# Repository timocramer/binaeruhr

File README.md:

This is a binary pocket watch, made with an atmega48pa. The enclosure is from a cheap pocket watch, mass produced in China and sold via Ebay or Aliexpress.

# build your own

Have a look at the [construction manual](construction-manual.md) if you want to build your own.

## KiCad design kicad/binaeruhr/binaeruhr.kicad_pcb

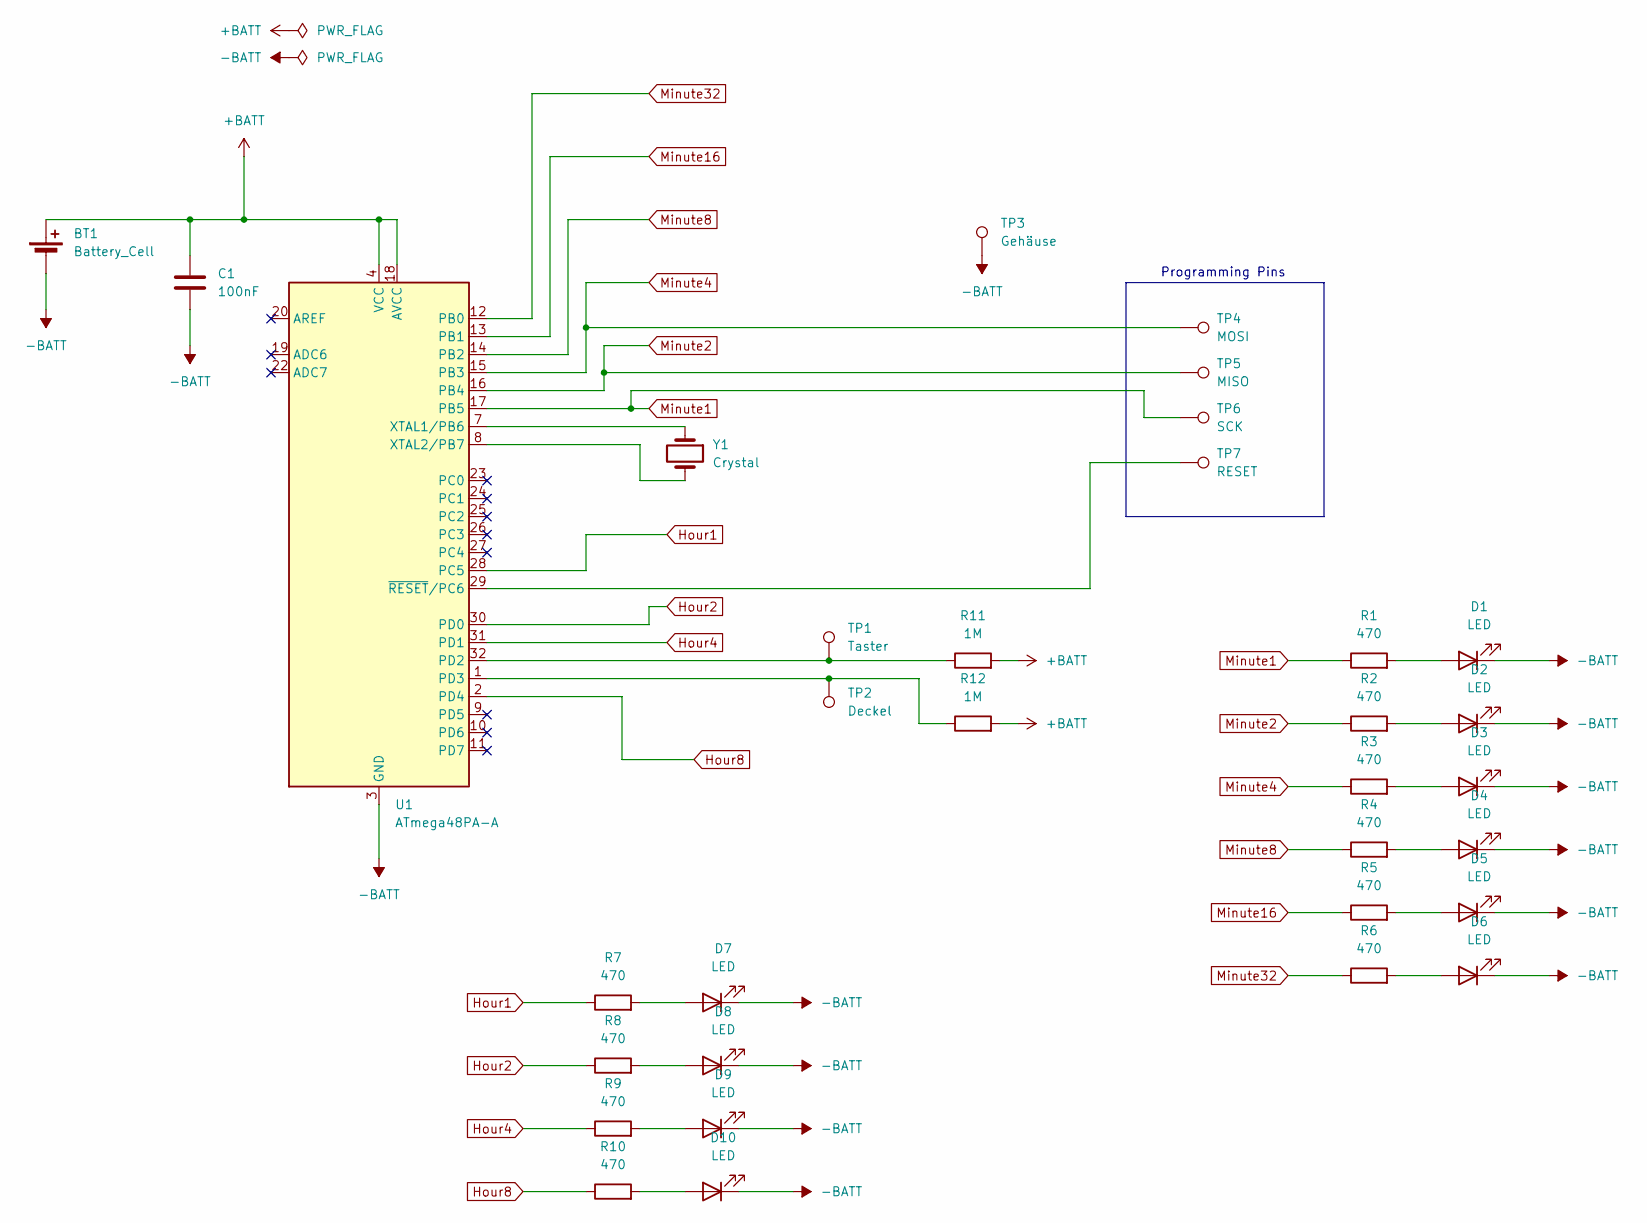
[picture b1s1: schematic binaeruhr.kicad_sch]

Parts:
BT1: Battery_Cell; BatteryHolder_Keystone_3002_1x2032
C1: 100nF; C_0805_2012Metric_Pad1.18x1.45mm_HandSolder
D1, D2, D3, D4, D5, D6, D7, D8, D9, D10: LED; LED_0805_2012Metric_Pad1.15x1.40mm_HandSolder
R1, R2, R3, R4, R5, R6, R7, R8, R9, R10: 470; R_0805_2012Metric_Pad1.20x1.40mm_HandSolder
R11, R12: 1M; R_0805_2012Metric_Pad1.20x1.40mm_HandSolder
TP1: Taster; TestPoint_Pad_4.0x4.0mm
TP2: Deckel; TestPoint_Pad_4.0x4.0mm
TP3: Gehäuse; TestPoint_Pad_2.0x2.0mm
TP4: MOSI; TestPoint_Pad_1.0x1.0mm
TP5: MISO; TestPoint_Pad_1.0x1.0mm
TP6: SCK; TestPoint_Pad_1.0x1.0mm
TP7: RESET; TestPoint_Pad_1.0x1.0mm
U1: ATmega48PA-A; TQFP-32_7x7mm_P0.8mm
Y1: Crystal; Crystal_SMD_MicroCrystal_MS1V-T1K

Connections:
+BATT: BT1.1 (+), C1.1, R11.2, R12.2, U1.4 (VCC), U1.6 (VCC), U1.18 (AVCC)
-BATT: BT1.2 (-), C1.2, D1.1 (K), D2.1 (K), D3.1 (K), D4.1 (K), D5.1 (K), D6.1 (K), D7.1 (K), D8.1 (K), D9.1 (K), D10.1 (K), TP3.1, U1.3 (GND), U1.5 (GND), U1.21 (GND)
Hour1: R7.1, U1.28 (PC5)
Hour2: R8.1, U1.30 (PD0)
Hour4: R9.1, U1.31 (PD1)
Hour8: R10.1, U1.2 (PD4)
Minute1: R1.1, TP6.1, U1.17 (PB5)
Minute2: R2.1, TP5.1, U1.16 (PB4)
Minute4: R3.1, TP4.1, U1.15 (PB3)
Minute8: R4.1, U1.14 (PB2)
Minute16: R5.1, U1.13 (PB1)
Minute32: R6.1, U1.12 (PB0)
unnamed: D1.2 (A), R1.2
unnamed: D2.2 (A), R2.2
unnamed: D3.2 (A), R3.2
unnamed: D4.2 (A), R4.2
unnamed: D5.2 (A), R5.2
unnamed: D6.2 (A), R6.2
unnamed: D7.2 (A), R7.2
unnamed: D8.2 (A), R8.2
unnamed: D9.2 (A), R9.2
unnamed: D10.2 (A), R10.2
unnamed: R11.1, TP1.1, U1.32 (PD2)
unnamed: R12.1, TP2.1, U1.1 (PD3)
unnamed: U1.7 (XTAL1/PB6), Y1.1
unnamed: U1.8 (XTAL2/PB7), Y1.2
unnamed: TP7.1, U1.29 (~RESET/PC6)

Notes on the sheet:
Programming Pins

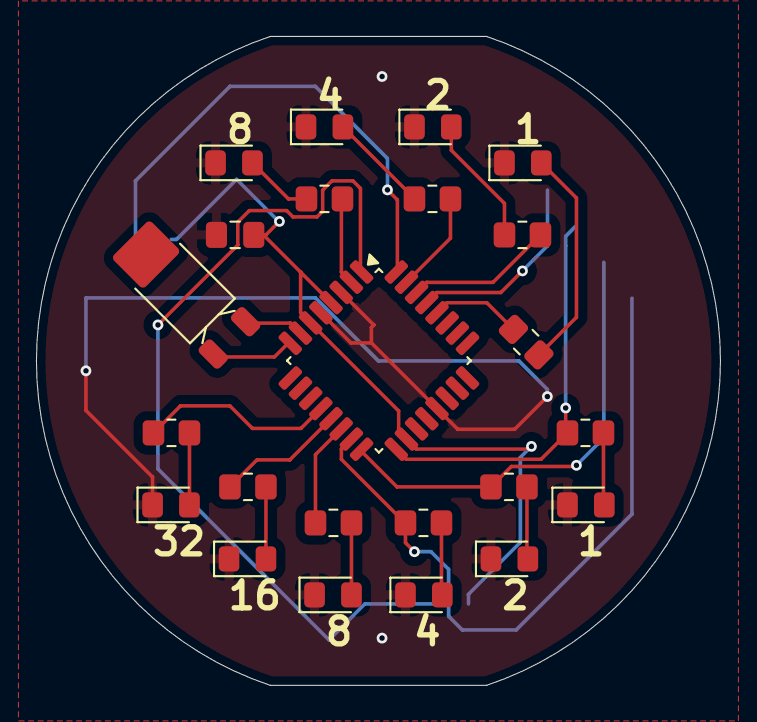
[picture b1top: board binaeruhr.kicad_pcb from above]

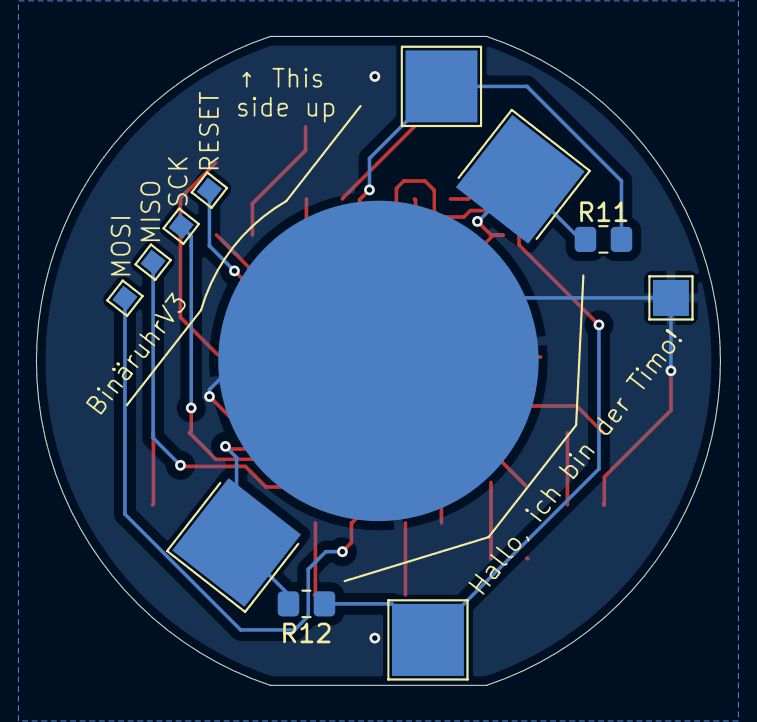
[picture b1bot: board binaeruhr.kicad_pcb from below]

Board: 2 copper layers, 38.0 x 36.0 mm, 33 parts (10 on the bottom side), 27 nets.

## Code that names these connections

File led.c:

#include "led.h"

#include <avr/io.h>

void led_init_outputs() {
    DDRD |= _BV(PD4); // hour8
    DDRD |= _BV(PD2); // hour4
    DDRD |= _BV(PD1); // hour2
    DDRC |= _BV(PC5); // hour1
    
    DDRB |= _BV(PB0); // minute32
    DDRB |= _BV(PB1); // minute16
    DDRB |= _BV(PB2); // minute8
    DDRB |= _BV(PB3); // minute4
    DDRB |= _BV(PB4); // minute2
    DDRB |= _BV(PB5); // minute1
}

static void hour8_on() {
    PORTD |= _BV(PD4);
}

static void hour8_off() {
    PORTD &= ~_BV(PD4);
}

static void hour4_on() {
    PORTD |= _BV(PD2);
}

static void hour4_off() {
    PORTD &= ~_BV(PD2);
}

static void hour2_on() {
    PORTD |= _BV(PD1);
}

static void hour2_off() {
    PORTD &= ~_BV(PD1);
}

static void hour1_on() {
    PORTC |= _BV(PC5);
}

static void hour1_off() {
    PORTC &= ~_BV(PC5);
}

void led_show_hours(uint8_t hours) {
    if(hours & 8) {
        hour8_on();
    } else {
        hour8_off();
    }
    if(hours & 4) {
        hour4_on();
    } else {
        hour4_off();
    }
    if(hours & 2) {
        hour2_on();
    } else {
        hour2_off();
    }
    if(hours & 1) {
        hour1_on();
    } else {
        hour1_off();
    }
}

static void minute32_on() {
    PORTB |= _BV(PB0);
}

static void minute32_off() {
    PORTB &= ~_BV(PB0);
}

static void minute16_on() {
    PORTB |= _BV(PB1);
}

static void minute16_off() {
    PORTB &= ~_BV(PB1);
}

static void minute8_on() {
    PORTB |= _BV(PB2);
}

static void minute8_off() {
    PORTB &= ~_BV(PB2);
}

static void minute4_on() {
    PORTB |= _BV(PB3);
}

static void minute4_off() {
    PORTB &= ~_BV(PB3);
}

static void minute2_on() {
    PORTB |= _BV(PB4);
}

static void minute2_off() {
    PORTB &= ~_BV(PB4);
}

static void minute1_on() {
    PORTB |= _BV(PB5);
}

static void minute1_off() {
    PORTB &= ~_BV(PB5);
}

void led_show_minutes(uint8_t minutes) {
    if(minutes & 32) {
        minute32_on();
    } else {
        minute32_off();
    }
    if(minutes & 16) {
        minute16_on();
    } else {
        minute16_off();
    }
    if(minutes & 8) {
        minute8_on();
    } else {
        minute8_off();
    }
    if(minutes & 4) {
        minute4_on();
    } else {
        minute4_off();
    }
    if(minutes & 2) {
        minute2_on();
    } else {
        minute2_off();
    }
    if(minutes & 1) {
        minute1_on();
    } else {
        minute1_off();
    }
}

void led_show_time(uint8_t hours, uint8_t minutes) {
    led_show_hours(hours);
    led_show_minutes(minutes);
}

void led_hours_off() {
    hour8_off();
    hour4_off();
    hour2_off();
    hour1_off();
}

void led_minutes_off() {
    minute32_off();
    minute16_off();
    minute8_off();
    minute4_off();
    minute2_off();
    minute1_off();
}

void leds_off() {
	led_hours_off();
	led_minutes_off();
}

void leds_on() {
    hour8_on();
    hour4_on();
    hour2_on();
    hour1_on();
    minute32_on();
    minute16_on();
    minute8_on();
    minute4_on();
    minute2_on();
    minute1_on();
}

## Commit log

2024-06-30 use correct function name, we disable the ac not adc
2024-07-01 changes in timer functions
    - fix prescaler 8 bits and add "prescaler" 1
    - more efficient implementation of current_timer_prescaler
    - reset timer conditionally but set timer bits unconditionally
2024-07-01 remove unused function
2024-07-01 alternative blink pattern on startup
2024-07-01 whitespace
2024-07-01 add function to init unused pins
2024-07-02 move going to time setting mode into an own function
2024-07-02 consistent indentation of switch cases
2024-07-02 use break instead of return so code after the switch is executed (no idea why the compiler was not warning this time)
2024-07-03 make constants uppercase, move some constants out of function
2024-07-03 use led pins for hour2 and hour4 that are used on the pcb
2024-07-04 reset timer on startup
2024-07-04 show time after blinking on startup
2024-07-04 add -Wshadow to CFLAGS
2024-07-04 move code into code directory
2024-07-04 use a copy instead of typecast, this looks cleaner
2024-07-04 cleanup headers
2024-07-04 add kicad files
2024-07-04 add README
2024-07-04 use consistent indentation in both C files
2024-07-04 add missing text above box
2024-07-06 show a circle on startup for debugging
2024-07-06 add new function to wait for a finished timer operation
2024-07-06 add function to reset unused timer registers
2024-07-06 add new blink pattern on startup
2024-07-06 set prescaler only when input is different from current value
2024-07-06 use while loop in normalize_time to be prepared for bigger hour values, as we can read random values from eeprom
2024-07-09 write the flash time to eeprom
2024-07-09 move time functions to localtime.c
2024-07-09 use better variable names in flash.sh
2024-07-09 give the option to write a distinct time instead of current time
2024-07-10 move initializing time from eeprom to an own function
2024-07-11 less repetition in led_show_bit_pattern
2024-07-11 make use of binary constants in led_show_bit_pattern
2024-07-11 make use of constexpr
2024-07-11 set show_leds_to_set to false on every state change
2024-07-11 remove parameter of show_time, it is called every time with watch_time
2024-07-11 call localtime functions by value and return new value
2024-07-11 add comment about how startup_circle_blink works
2024-07-11 add const to button_up_at
2024-07-11 remove leds_on, as it is unused
2024-07-11 move via away from "Hallo, ich bin der Timo!"
2024-07-23 check for last LED, not the the bit after that in startup_circle_blink
2024-07-23 remove useless return statement
2024-07-23 remove intermediate calls to wait_for_finished_timer_operation, every register has it's own buffer
2024-07-23 call wait_for_finished_timer_operation in set_timer2_prescaler only when something should be changed
2024-07-24 call normalize_time in load_time_from_eeprom, the result should be valid
2024-07-24 set timer values on every button press, not only when lid is open
    this could fix issue #1
2024-07-28 add construction manual
2024-07-28 include in the manual when the battery has to be inserted
2024-07-28 link fron README to the construction manual
2024-07-28 lower instead of upper
2024-07-28 add manual how to use the watch
2024-08-01 typo 3032 -> 2032
2024-09-29 use grouping to turn testing points with closer spacing. This should make Flashing easier
2025-06-18 add comment about SECOND_INCREMENT
2025-10-27 remove unnecessary semicolons
2025-10-30 shorter flash script
2025-10-30 move mode setting into own functions
2025-12-04 shine only for a maximum amount of time
    this solves issue #5
